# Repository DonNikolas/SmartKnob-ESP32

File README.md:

# SmartKnob-ESP32
Sound-controlled haptic smart knob for smart home control — ESP32-S3, FOC motor feedback, clap detection, MQTT/Home Assistant

## 3D-Render

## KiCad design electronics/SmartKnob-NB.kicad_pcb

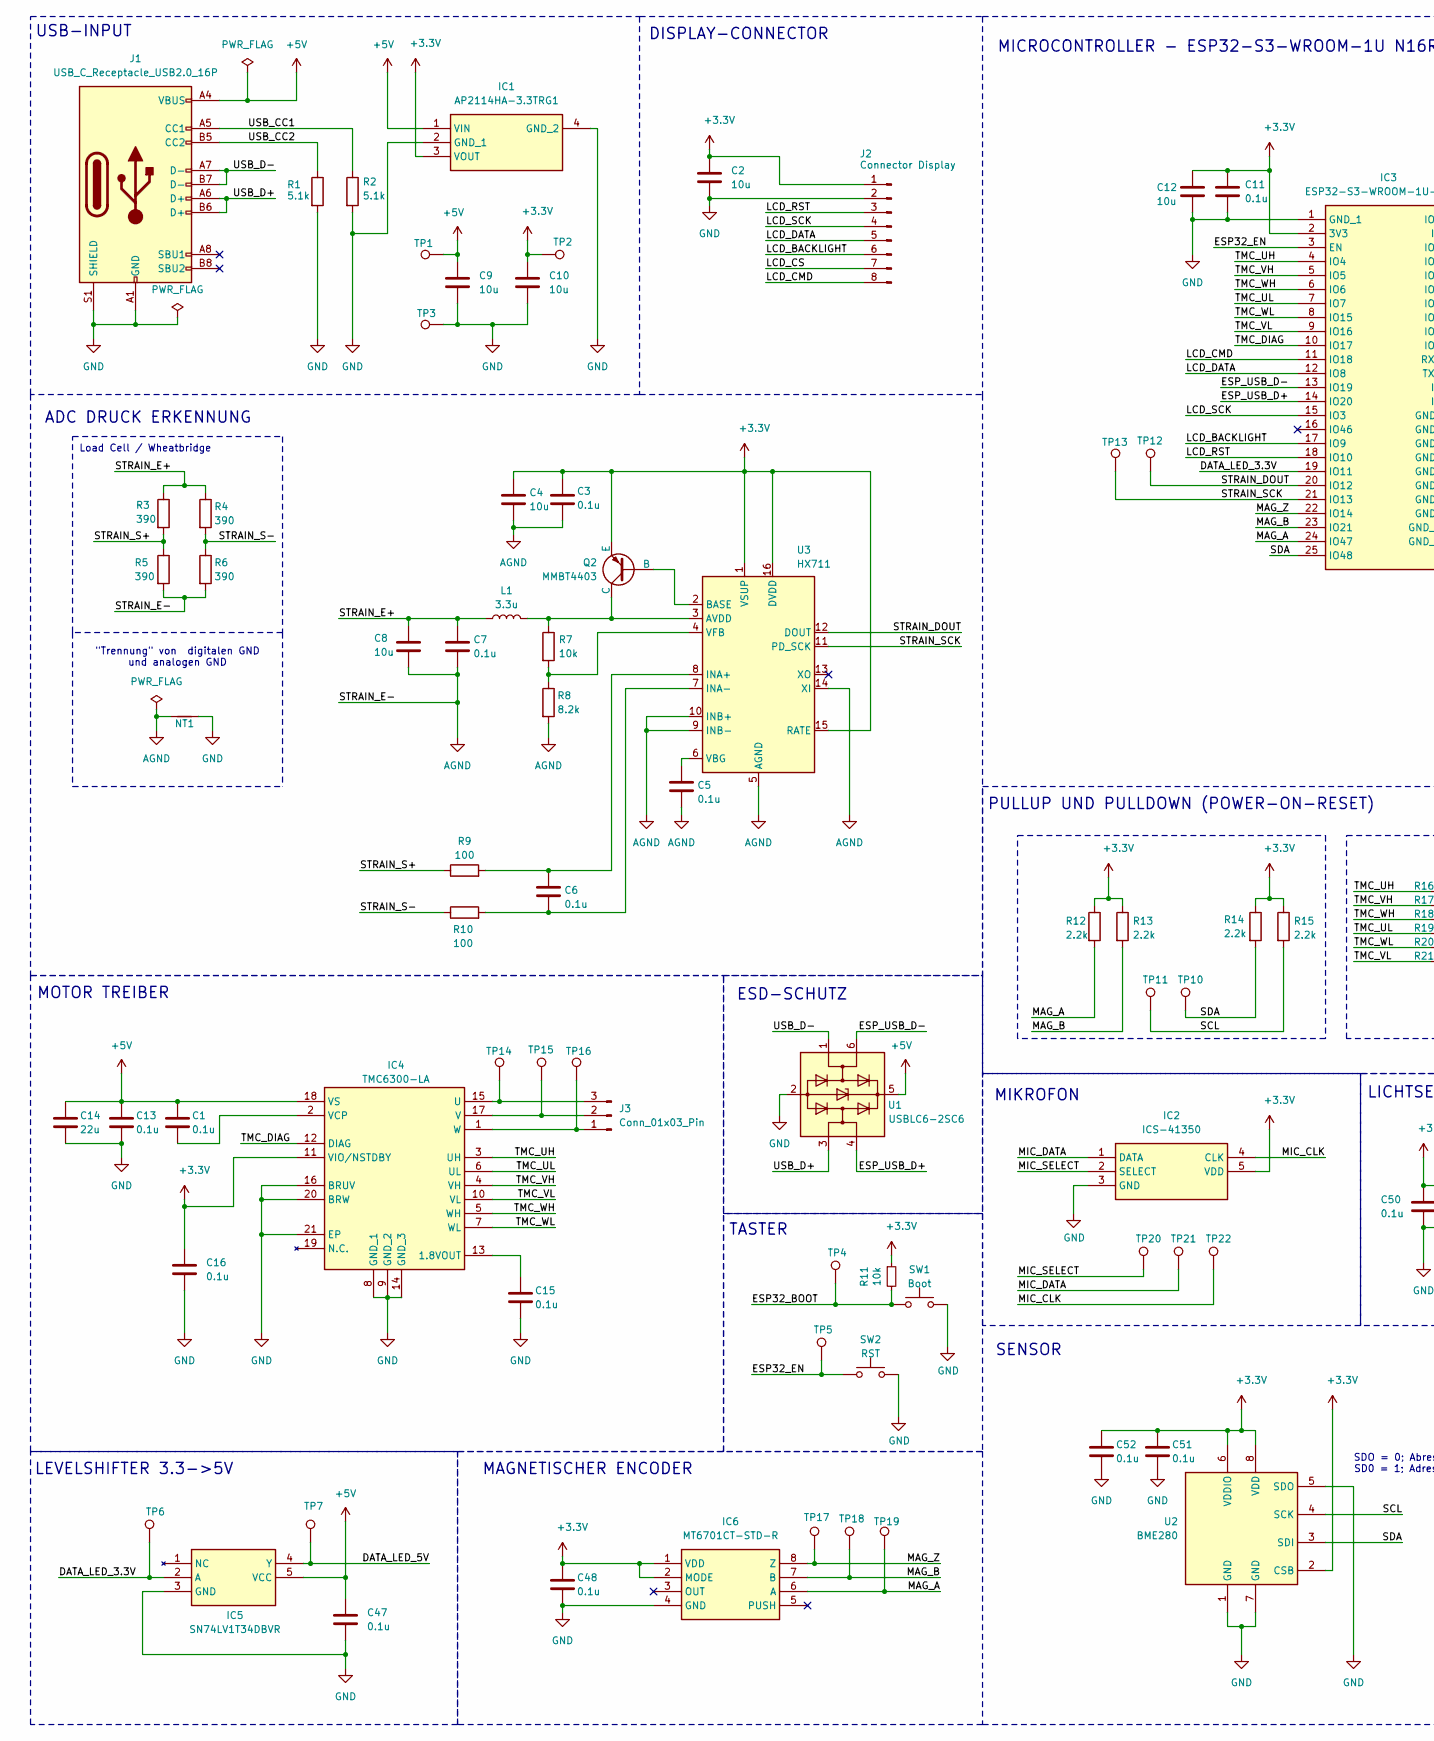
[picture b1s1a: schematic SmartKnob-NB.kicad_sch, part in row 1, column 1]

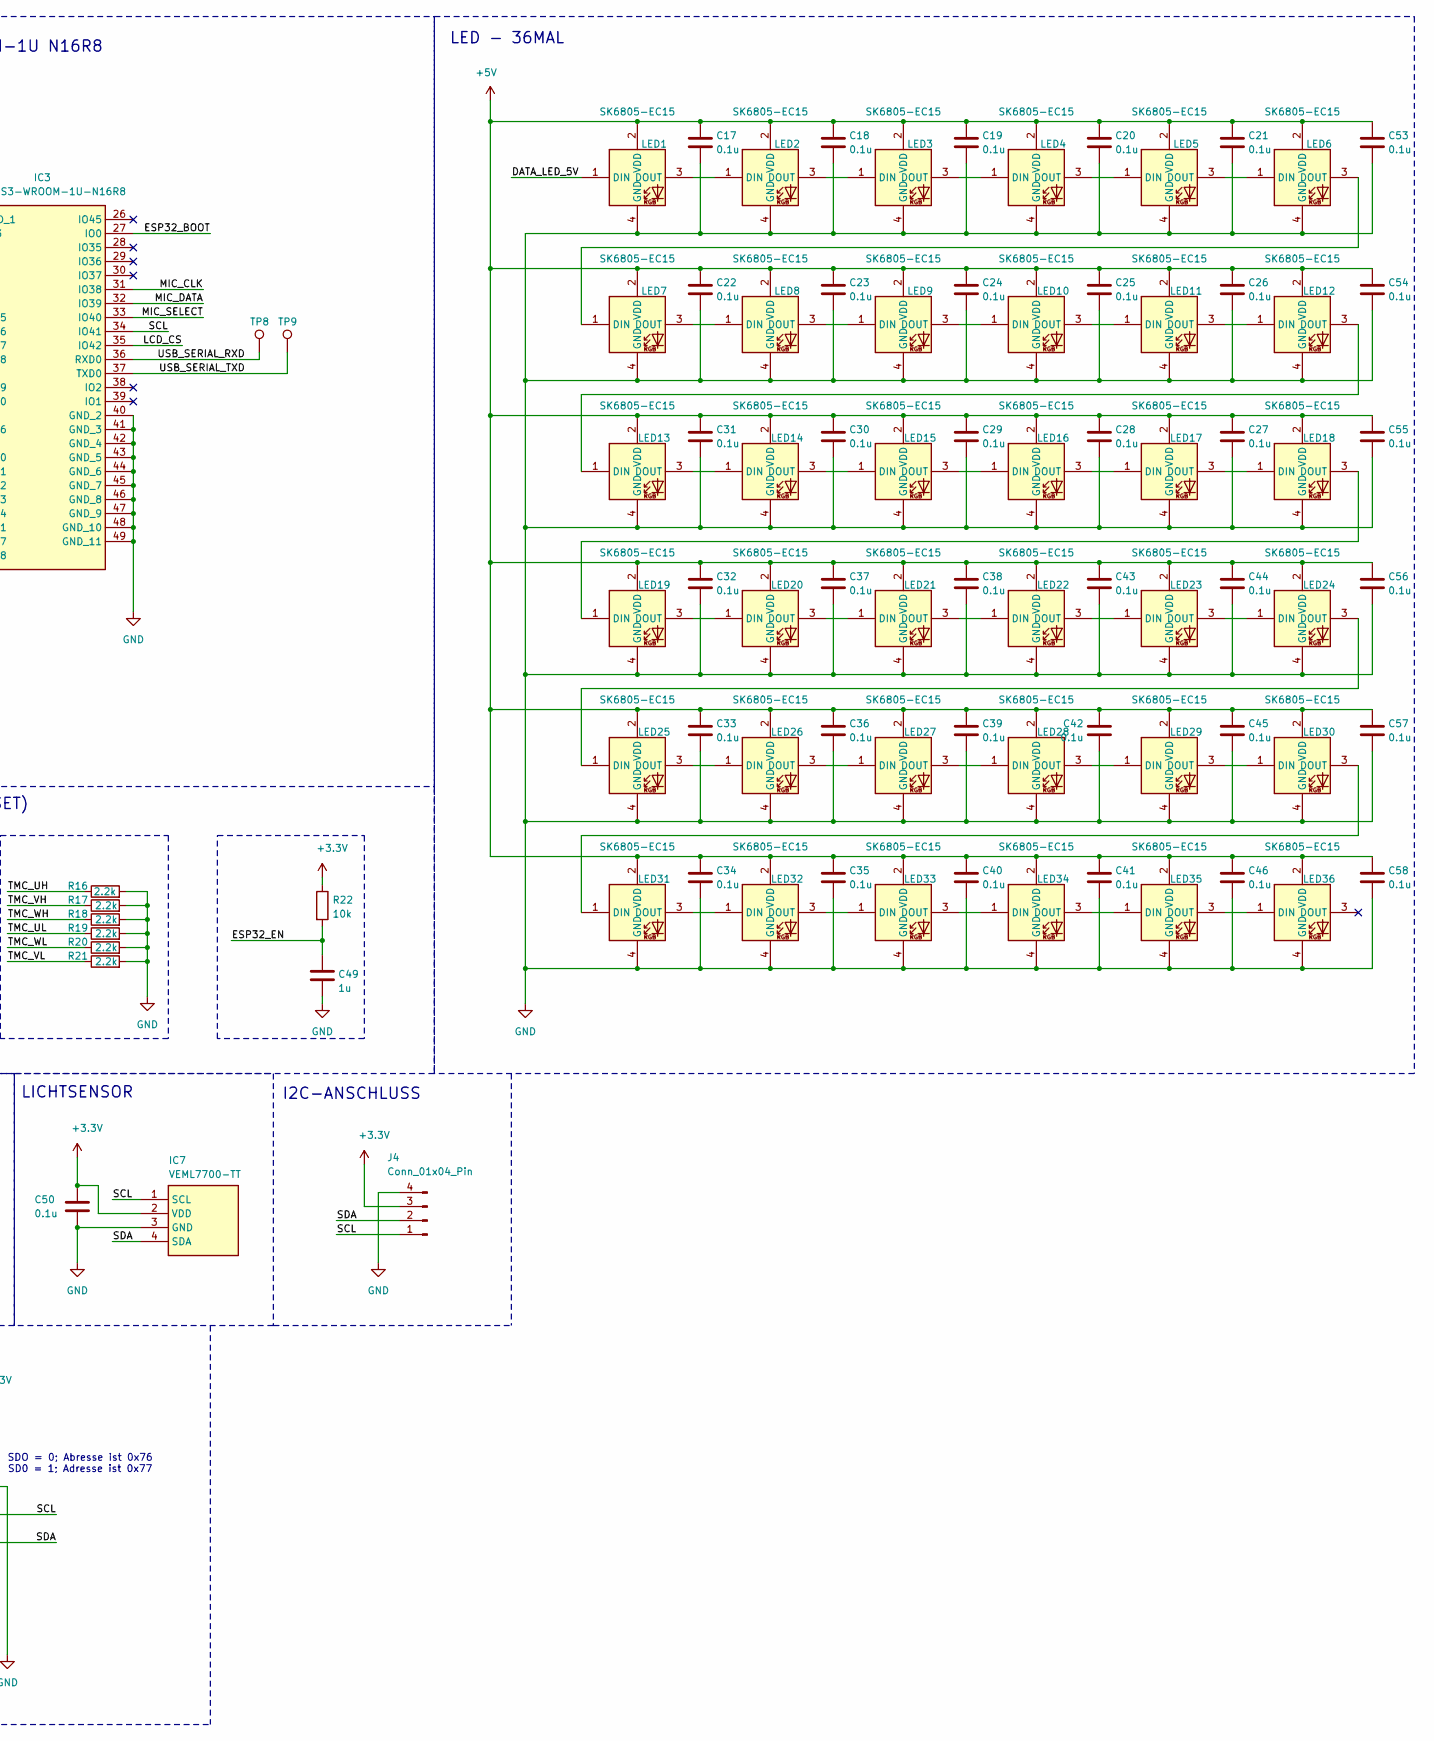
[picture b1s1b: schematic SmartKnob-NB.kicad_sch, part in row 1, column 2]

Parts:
C1, C3, C5, C6, C7, C11, C13, C15, C16, C17, C18, C19, C20, C21, C22, C23, C24, C25, C26, C27, C28, C29, C30, C31, C32, C33, C34, C35, C36, C37, C38, C39, C40, C41, C42, C43, C44, C45, C46, C47, C48, C50, C51, C52, C53, C54, C55, C56, C57, C58: 0.1u; C_0402_1005Metric_Pad0.74x0.62mm_HandSolder
C2, C9, C10, C12: 10u; C_0603_1608Metric_Pad1.08x0.95mm_HandSolder
C4, C8: 10u; C_0805_2012Metric_Pad1.18x1.45mm_HandSolder
C14: 22u; C_0603_1608Metric_Pad1.08x0.95mm_HandSolder
C49: 1u; C_0603_1608Metric_Pad1.08x0.95mm_HandSolder
IC1: AP2114HA-3.3TRG1; SOT230P700X180-4N; Manufacturer_Part_Number AP2114HA-3.3TRG1; Mouser Part Number 621-AP2114HA-3.3TRG1
IC2: ICS-41350; ICS41352; Manufacturer_Part_Number ICS-41350; Mouser Part Number 410-ICS-41350
IC3: ESP32-S3-WROOM-1U-N16R8; ESP32S3WROOM1UN16R8; Manufacturer_Part_Number ESP32-S3-WROOM-1U-N16R8; Mouser Part Number 356-ESP32S3WM1UN16R8
IC4: TMC6300-LA; QFN40P300X300X90-21N; Manufacturer_Part_Number TMC6300-LA; Mouser Part Number 700-TMC6300-LA
IC5: SN74LV1T34DBVR; SOT95P280X145-5N; Manufacturer_Part_Number SN74LV1T34DBVR; Mouser Part Number 595-SN74LV1T34DBVR
IC6: MT6701CT-STD-R; SOIC127P600X175-8N; Manufacturer_Part_Number MT6701CT-STD-R
IC7: VEML7700-TT; VEML7700; Manufacturer_Part_Number VEML7700-TT; Mouser Part Number 78-VEML7700-TT
J1: USB_C_Receptacle_USB2.0_16P; USB4510031A
J2: Connector Display; Unbenannt
J3: Conn_01x03_Pin; Molex_CLIK-Mate_502386-0370_1x03-1MP_P1.25mm_Horizontal
J4: Conn_01x04_Pin; Unbenannt
L1: 3.3u; L_0805_2012Metric_Pad1.05x1.20mm_HandSolder
LED1, LED2, LED3, LED4, LED5, LED6, LED7, LED8, LED9, LED10, LED11, LED12, LED13, LED14, LED15, LED16, LED17, LED18, LED19, LED20, LED21, LED22, LED23, LED24, LED25, LED26, LED27, LED28, LED29, LED30, LED31, LED32, LED33, LED34, LED35, LED36: SK6805-EC15; SK6805EC15; Manufacturer_Part_Number SK6805-EC15
NT1: NetTie_2; NetTie-2_SMD_Pad0.5mm
Q2: MMBT4403; SOT95P248X115-3N
R1, R2: 5.1k; R_0402_1005Metric_Pad0.72x0.64mm_HandSolder
R3, R4, R5, R6: 390; D_2512_6332Metric
R7, R22: 10k; R_0402_1005Metric_Pad0.72x0.64mm_HandSolder
R8: 8.2k; R_0402_1005Metric_Pad0.72x0.64mm_HandSolder
R9, R10: 100; R_0402_1005Metric_Pad0.72x0.64mm_HandSolder
R11: 10k; R_0402_1005Metric_Pad0.72x0.64mm_HandSolder; LCSC C98220
R12, R13, R14, R15, R16, R17, R18, R19, R20, R21: 2.2k; R_0402_1005Metric_Pad0.72x0.64mm_HandSolder
SW1: Boot; KSS241GLFS; LCSC C116501
SW2: RST; KSS241GLFS; LCSC C116501
TP1, TP2, TP3, TP4, TP5, TP6, TP7, TP8, TP9, TP10, TP11, TP12, TP13, TP14, TP15, TP16, TP17, TP18, TP19, TP20, TP21, TP22: TestPoint; TestPoint_Pad_1.5x1.5mm
U1: USBLC6-2SC6; SOT-23-6_Handsoldering; LCSC C7519
U2: BME280; Bosch_LGA-8_2.5x2.5mm_P0.65mm_ClockwisePinNumbering
U3: HX711; SOP-16_4.4x10.4mm_P1.27mm

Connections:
+3.3V: C2.1, C3.1, C4.1, C10.1, C11.1, C12.1, C16.1, C48.1, C50.1, C51.1, C52.1, IC1.3 (VOUT), IC2.5 (VDD), IC3.2 (3V3), IC4.11 (VIO/NSTDBY), IC6.1 (VDD), IC6.2 (MODE), IC7.2 (VDD), J2.1, J4.3, Q2.3 (E), R11.1, R12.1, R13.1, R14.1, R15.1, R22.1, TP2.1 (1_1), U2.2 (CSB), U2.6 (VDDIO), U2.8 (VDD), U3.1 (VSUP), U3.15 (RATE), U3.16 (DVDD)
+5V: C1.1, C9.1, C13.1, C14.1, C17.1, C18.1, C19.1, C20.1, C21.1, C22.1, C23.1, C24.1, C25.1, C26.1, C27.1, C28.1, C29.1, C30.1, C31.1, C32.1, C33.1, C34.1, C35.1, C36.1, C37.1, C38.1, C39.1, C40.1, C41.1, C42.1, C43.1, C44.1, C45.1, C46.1, C47.1, C53.1, C54.1, C55.1, C56.1, C57.1, C58.1, IC1.1 (VIN), IC4.18 (VS), IC5.5 (VCC), J1.A4 (VBUS), J1.A9 (VBUS), J1.B4 (VBUS), J1.B9 (VBUS), LED1.2 (VDD), LED2.2 (VDD), LED3.2 (VDD), LED4.2 (VDD), LED5.2 (VDD), LED6.2 (VDD), LED7.2 (VDD), LED8.2 (VDD), LED9.2 (VDD), LED10.2 (VDD), LED11.2 (VDD), LED12.2 (VDD), LED13.2 (VDD), LED14.2 (VDD), LED15.2 (VDD), LED16.2 (VDD), LED17.2 (VDD), LED18.2 (VDD), LED19.2 (VDD), LED20.2 (VDD), LED21.2 (VDD), LED22.2 (VDD), LED23.2 (VDD), LED24.2 (VDD), LED25.2 (VDD), LED26.2 (VDD), LED27.2 (VDD), LED28.2 (VDD), LED29.2 (VDD), LED30.2 (VDD), LED31.2 (VDD), LED32.2 (VDD), LED33.2 (VDD), LED34.2 (VDD), LED35.2 (VDD), LED36.2 (VDD), TP1.1 (1_1), U1.5 (VBUS)
/DATA_LED_3.3V: IC3.19 (IO11), IC5.2 (A), TP6.1 (1_1)
/DATA_LED_5V: IC5.4 (Y), LED1.1 (DIN), TP7.1 (1_1)
/ESP32_BOOT: IC3.27 (IO0), R11.2, SW1.1, TP4.1 (1_1)
/ESP32_EN: C49.1, IC3.3 (EN), R22.2, SW2.1, TP5.1 (1_1)
/ESP_USB_D+: IC3.14 (IO20), U1.4 (I/O2)
/ESP_USB_D-: IC3.13 (IO19), U1.6 (I/O1)
/LCD_BACKLIGHT: IC3.17 (IO9), J2.6
/LCD_CMD: IC3.11 (IO18), J2.8
/LCD_CS: IC3.35 (IO42), J2.7
/LCD_DATA: IC3.12 (IO8), J2.5
/LCD_RST: IC3.18 (IO10), J2.3
/LCD_SCK: IC3.15 (IO3), J2.4
/MAG_A: IC3.24 (IO47), IC6.6 (A), R12.2, TP19.1 (1_1)
/MAG_B: IC3.23 (IO21), IC6.7 (B), R13.2, TP18.1 (1_1)
/MAG_Z: IC3.22 (IO14), IC6.8 (Z), TP17.1 (1_1)
/MIC_CLK: IC2.4 (CLK), IC3.31 (IO38), TP22.1 (1_1)
/MIC_DATA: IC2.1 (DATA), IC3.32 (IO39), TP21.1 (1_1)
/MIC_SELECT: IC2.2 (SELECT), IC3.33 (IO40), TP20.1 (1_1)
/SCL: IC3.34 (IO41), IC7.1 (SCL), J4.1, R15.2, TP11.1 (1_1), U2.4 (SCK)
/SDA: IC3.25 (IO48), IC7.4 (SDA), J4.2, R14.2, TP10.1 (1_1), U2.3 (SDI)
/STRAIN_DOUT: IC3.20 (IO12), TP12.1 (1_1), U3.12 (DOUT)
/STRAIN_E+: C7.1, C8.1, L1.1, R3.1, R4.1
/STRAIN_S+: R3.2, R5.1, R9.1
/STRAIN_S-: R4.2, R6.1, R10.1
/STRAIN_SCK: IC3.21 (IO13), TP13.1 (1_1), U3.11 (PD_SCK)
/TMC_DIAG: IC3.10 (IO17), IC4.12 (DIAG)
/TMC_UH: IC3.4 (IO4), IC4.3 (UH), R16.1
/TMC_UL: IC3.7 (IO7), IC4.6 (UL), R19.1
/TMC_VH: IC3.5 (IO5), IC4.4 (VH), R17.1
/TMC_VL: IC3.9 (IO16), IC4.10 (VL), R21.1
/TMC_WH: IC3.6 (IO6), IC4.5 (WH), R18.1
/TMC_WL: IC3.8 (IO15), IC4.7 (WL), R20.1
/USB_CC1: J1.A5 (CC1), R2.1
/USB_CC2: J1.B5 (CC2), R1.1
/USB_D+: J1.A6 (D+), J1.B6 (D+), U1.3 (I/O2)
/USB_D-: J1.A7 (D-), J1.B7 (D-), U1.1 (I/O1)
/USB_SERIAL_RXD: IC3.36 (RXD0), TP8.1 (1_1)
/USB_SERIAL_TXD: IC3.37 (TXD0), TP9.1 (1_1)
AGND: C3.2, C4.2, C5.2, C7.2, C8.2, NT1.1, R5.2, R6.2, R8.2, U3.5 (AGND), U3.9 (INB-), U3.10 (INB+), U3.14 (XI)
GND: C2.2, C9.2, C10.2, C11.2, C12.2, C13.2, C14.2, C15.2, C16.2, C17.2, C18.2, C19.2, C20.2, C21.2, C22.2, C23.2, C24.2, C25.2, C26.2, C27.2, C28.2, C29.2, C30.2, C31.2, C32.2, C33.2, C34.2, C35.2, C36.2, C37.2, C38.2, C39.2, C40.2, C41.2, C42.2, C43.2, C44.2, C45.2, C46.2, C47.2, C48.2, C49.2, C50.2, C51.2, C52.2, C53.2, C54.2, C55.2, C56.2, C57.2, C58.2, IC1.2 (GND_1), IC1.4 (GND_2), IC2.3 (GND), IC3.1 (GND_1), IC3.40 (GND_2), IC3.41 (GND_3), IC3.42 (GND_4), IC3.43 (GND_5), IC3.44 (GND_6), IC3.45 (GND_7), IC3.46 (GND_8), IC3.47 (GND_9), IC3.48 (GND_10), IC3.49 (GND_11), IC4.8 (GND_1), IC4.9 (GND_2), IC4.14 (GND_3), IC4.16 (BRUV), IC4.20 (BRW), IC4.21 (EP), IC5.3 (GND), IC6.4 (GND), IC7.3 (GND), J1.A1 (GND), J1.A12 (GND), J1.B1 (GND), J1.B12 (GND), J1.S1 (SHIELD), J2.2, J4.4, LED1.4 (GND), LED2.4 (GND), LED3.4 (GND), LED4.4 (GND), LED5.4 (GND), LED6.4 (GND), LED7.4 (GND), LED8.4 (GND), LED9.4 (GND), LED10.4 (GND), LED11.4 (GND), LED12.4 (GND), LED13.4 (GND), LED14.4 (GND), LED15.4 (GND), LED16.4 (GND), LED17.4 (GND), LED18.4 (GND), LED19.4 (GND), LED20.4 (GND), LED21.4 (GND), LED22.4 (GND), LED23.4 (GND), LED24.4 (GND), LED25.4 (GND), LED26.4 (GND), LED27.4 (GND), LED28.4 (GND), LED29.4 (GND), LED30.4 (GND), LED31.4 (GND), LED32.4 (GND), LED33.4 (GND), LED34.4 (GND), LED35.4 (GND), LED36.4 (GND), NT1.2, R1.2, R2.2, R16.2, R17.2, R18.2, R19.2, R20.2, R21.2, SW1.2, SW2.2, TP3.1 (1_1), U1.2 (GND), U2.1 (GND), U2.5 (SDO), U2.7 (GND)
unnamed: C15.1, IC4.13 (1.8VOUT)
unnamed: IC4.15 (U), J3.3, TP14.1 (1_1)
unnamed: IC4.17 (V), J3.2, TP15.1 (1_1)
unnamed: C1.2, IC4.2 (VCP)
unnamed: IC4.1 (W), J3.1, TP16.1 (1_1)
unnamed: LED1.3 (DOUT), LED2.1 (DIN)
unnamed: LED2.3 (DOUT), LED3.1 (DIN)
unnamed: LED3.3 (DOUT), LED4.1 (DIN)
unnamed: LED4.3 (DOUT), LED5.1 (DIN)
unnamed: LED5.3 (DOUT), LED6.1 (DIN)
unnamed: LED6.3 (DOUT), LED7.1 (DIN)
unnamed: LED7.3 (DOUT), LED8.1 (DIN)
unnamed: LED8.3 (DOUT), LED9.1 (DIN)
unnamed: LED9.3 (DOUT), LED10.1 (DIN)
unnamed: LED10.3 (DOUT), LED11.1 (DIN)
unnamed: LED11.3 (DOUT), LED12.1 (DIN)
unnamed: LED12.3 (DOUT), LED13.1 (DIN)
unnamed: LED13.3 (DOUT), LED14.1 (DIN)
unnamed: LED14.3 (DOUT), LED15.1 (DIN)
unnamed: LED15.3 (DOUT), LED16.1 (DIN)
unnamed: LED16.3 (DOUT), LED17.1 (DIN)
unnamed: LED17.3 (DOUT), LED18.1 (DIN)
unnamed: LED18.3 (DOUT), LED19.1 (DIN)
unnamed: LED19.3 (DOUT), LED20.1 (DIN)
unnamed: LED20.3 (DOUT), LED21.1 (DIN)
unnamed: LED21.3 (DOUT), LED22.1 (DIN)
unnamed: LED22.3 (DOUT), LED23.1 (DIN)
unnamed: LED23.3 (DOUT), LED24.1 (DIN)
unnamed: LED24.3 (DOUT), LED25.1 (DIN)
unnamed: LED25.3 (DOUT), LED26.1 (DIN)
unnamed: LED26.3 (DOUT), LED27.1 (DIN)
unnamed: LED27.3 (DOUT), LED28.1 (DIN)
unnamed: LED28.3 (DOUT), LED29.1 (DIN)
unnamed: LED29.3 (DOUT), LED30.1 (DIN)
unnamed: LED30.3 (DOUT), LED31.1 (DIN)
unnamed: LED31.3 (DOUT), LED32.1 (DIN)
unnamed: LED32.3 (DOUT), LED33.1 (DIN)
unnamed: LED33.3 (DOUT), LED34.1 (DIN)
unnamed: LED34.3 (DOUT), LED35.1 (DIN)
unnamed: LED35.3 (DOUT), LED36.1 (DIN)
unnamed: Q2.2 (B), U3.2 (BASE)
unnamed: L1.2, Q2.1 (C), R7.1, U3.3 (AVDD)
unnamed: C6.1, R9.2, U3.8 (INA+)
unnamed: C6.2, R10.2, U3.7 (INA-)
unnamed: C5.1, U3.6 (VBG)
unnamed: R7.2, R8.1, U3.4 (VFB)

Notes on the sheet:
LEVELSHIFTER 3.3->5V
TASTER
ADC DRUCK ERKENNUNG
Load Cell / Wheatbridge
I2C-ANSCHLUSS
LED - 36MAL
"Trennung" von digitalen GND und analogen GND
MAGNETISCHER ENCODER
USB-INPUT
SENSOR
MICROCONTROLLER - ESP32-S3-WROOM-1U N16R8
MOTOR TREIBER
MIKROFON
LICHTSENSOR
SDO = 0; Abresse ist 0x76 SD0 = 1; Adresse ist 0x77
PULLUP UND PULLDOWN (POWER-ON-RESET)
ESD-SCHUTZ
DISPLAY-CONNECTOR

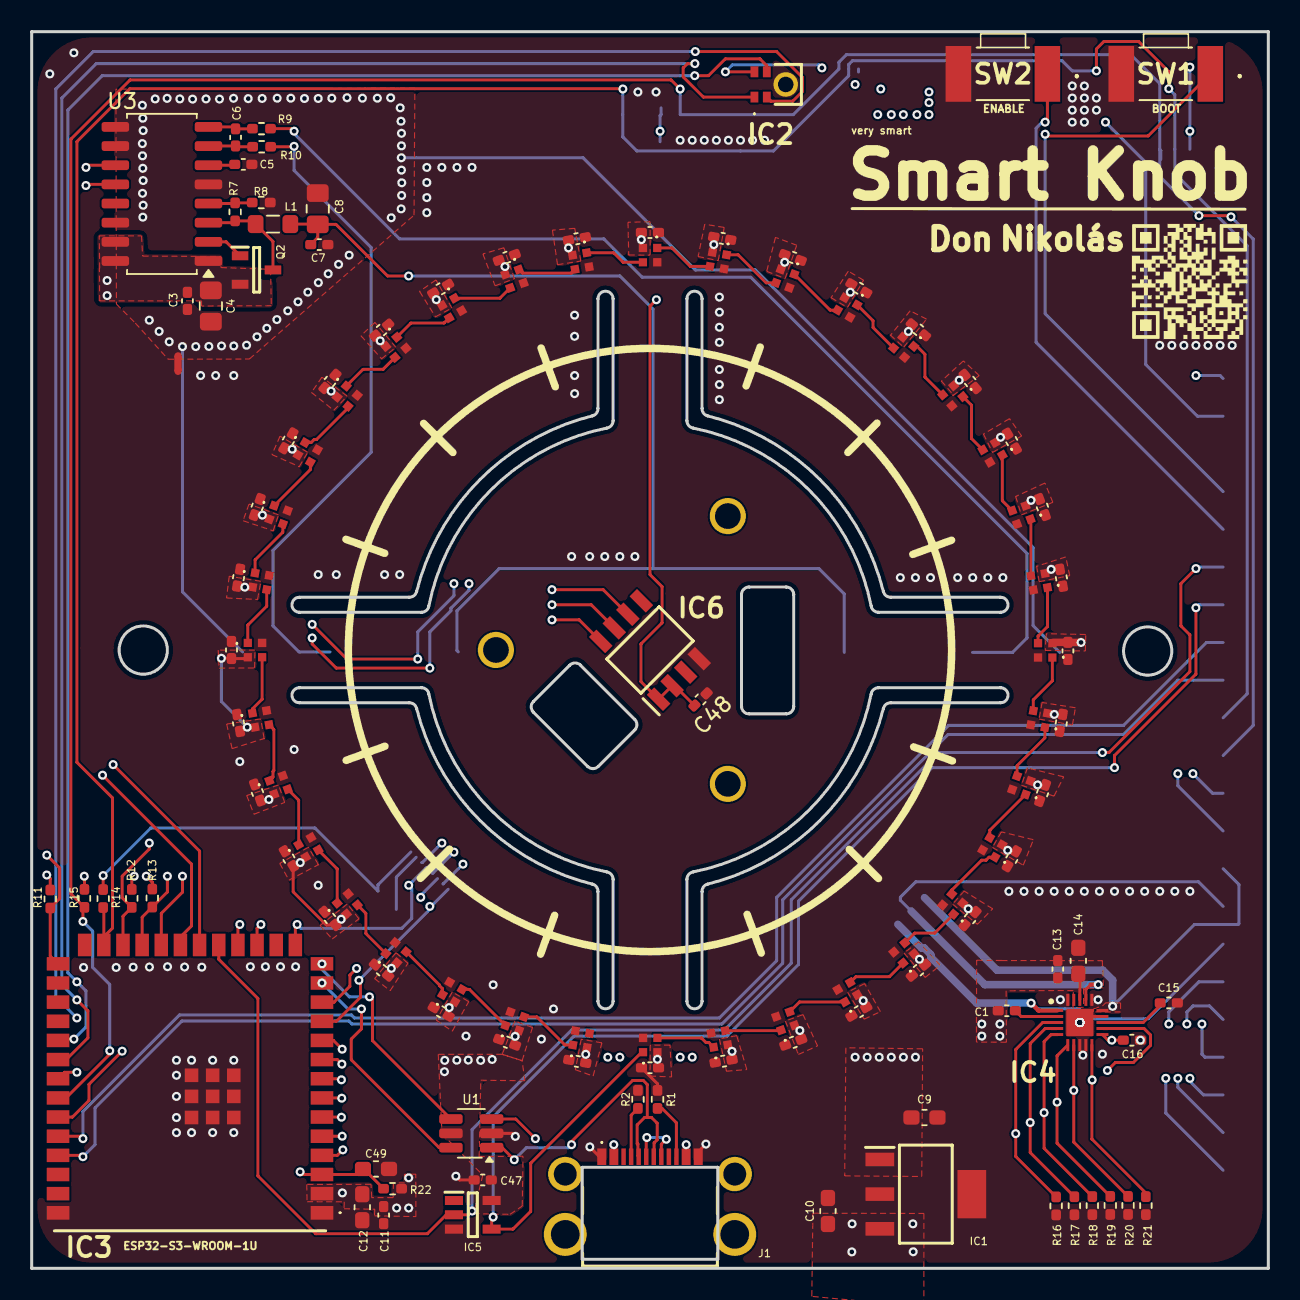
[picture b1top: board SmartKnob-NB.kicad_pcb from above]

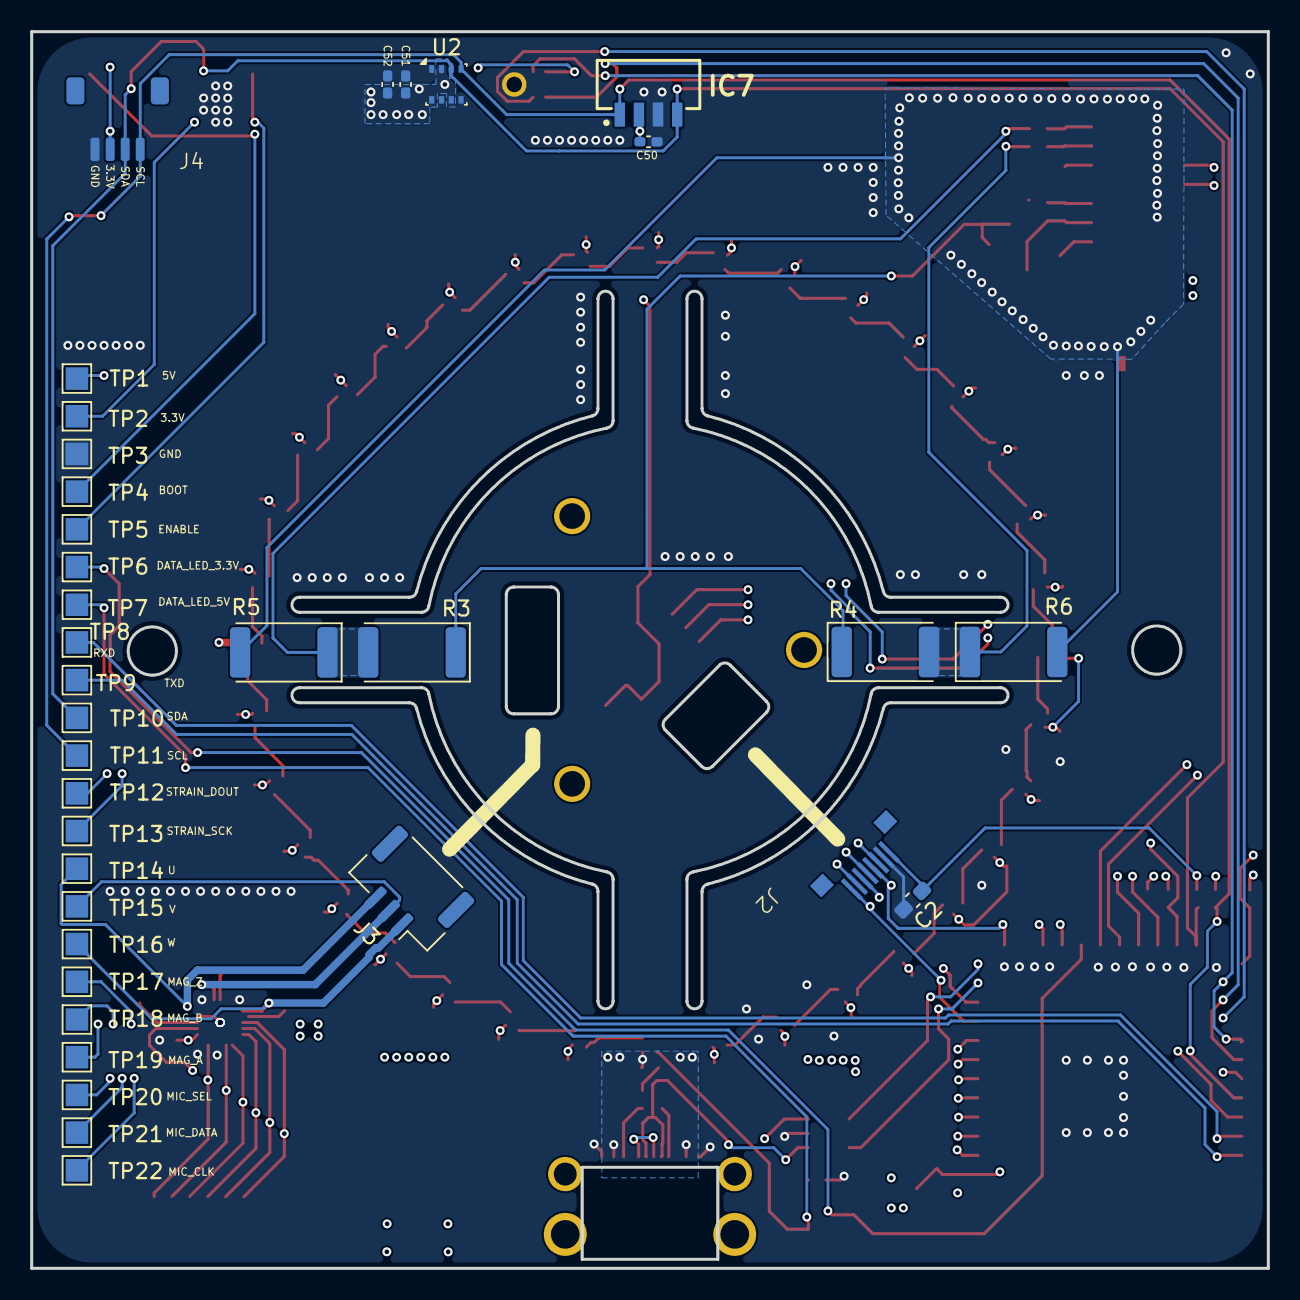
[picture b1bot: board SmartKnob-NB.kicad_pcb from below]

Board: 4 copper layers, 82.0 x 82.0 mm, 157 parts (35 on the bottom side), 88 nets.

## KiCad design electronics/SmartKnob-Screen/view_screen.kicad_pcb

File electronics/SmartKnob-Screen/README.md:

# SmartKnob Screen PCB

The screen PCB design was copied unchanged from SeedLabs.

Source: https://github.com/SeedLabs-it/smartknob-hardware

The original files are stored here for use with my SmartKnob project.
This PCB was not designed by me.

See license.md for the original SeedLabs hardware license.

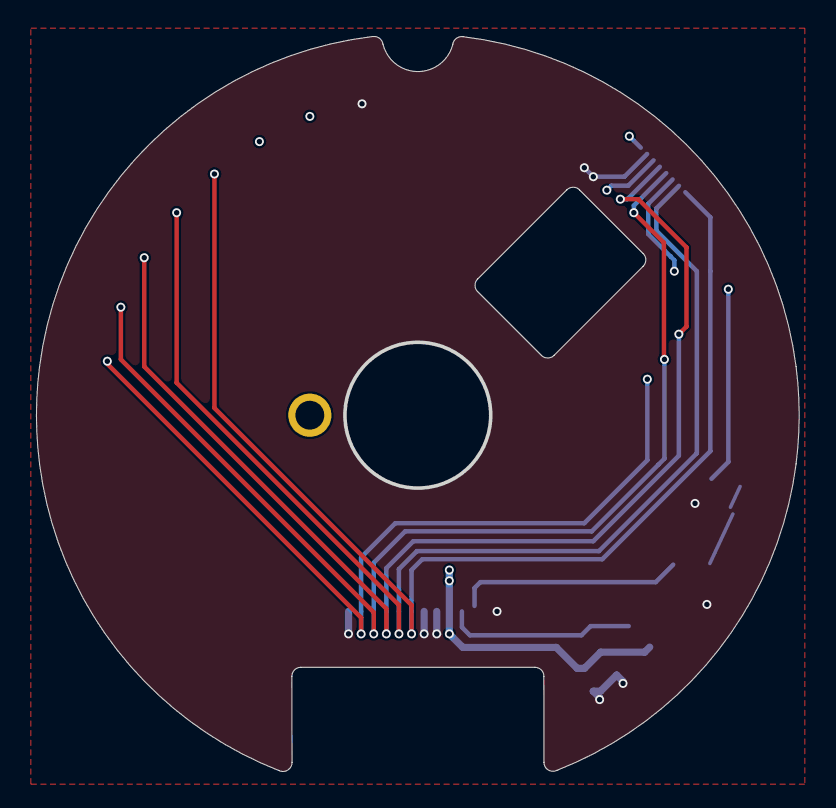
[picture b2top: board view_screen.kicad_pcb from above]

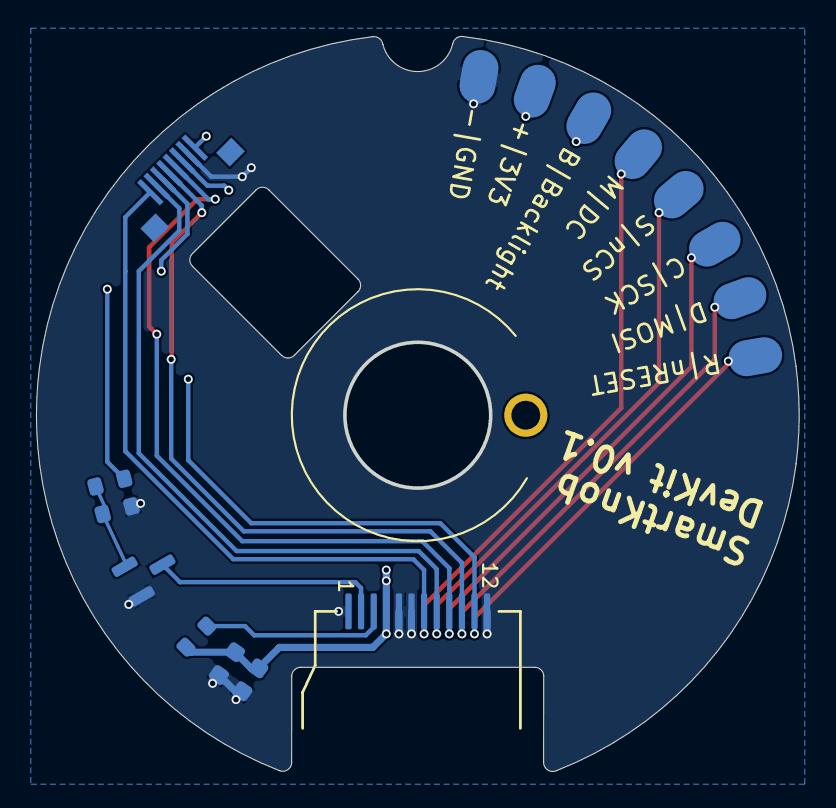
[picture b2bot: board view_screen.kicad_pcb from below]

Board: 4 copper layers, 42.4 x 40.8 mm, 17 parts (16 on the bottom side), 11 nets.

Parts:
C1: 22uF; C_0603_1608Metric
C2: 0.1uF; C_0603_1608Metric
H1: AlignmentHole; AlignmentHole_1.6
J2: GC9A01; GC9A01Round1.28
J6: LCD - FPC; Amphenol FCI FPC 8 pin 0.5 pitch
Q1: 2N7002; SOT-23
R1: 10k; R_0603_1608Metric
R2: 22R; R_0603_1608Metric
R3: 1M; R_0603_1608Metric
TP1: S|nCS; test_point_connectivity
TP2: C|SCK; test_point_connectivity
TP3: D|MOSI; test_point_connectivity
TP4: R|nRESET; test_point_connectivity
TP5: -|GND; test_point_connectivity
TP6: +|3V3; test_point_connectivity
TP7: B|Backlight; test_point_connectivity
TP8: M|DC; test_point_connectivity

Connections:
/BACKLIGHT_EN: J6.3, R1.1, TP7.1
/DC: J2.7, J6.1, TP8.1
/LEDA: J2.3, R2.2
/LEDK: J2.2, Q1.3 (D)
/MOSI: J2.10, J6.4, TP3.1
/SCK: J2.9, J6.5, TP2.1
/VDD: C1.1, C2.1, J2.4, J6.8, R2.1, TP6.1
/nCS: J2.8, J6.2, TP1.1
/nRESET: J2.11, J6.6, TP4.1
GND: C1.2, C2.2, J2.1, J2.5, J2.6, J2.12, J6.7, Q1.2 (S), R3.2, TP5.1
unnamed: Q1.1 (G), R1.2, R3.1

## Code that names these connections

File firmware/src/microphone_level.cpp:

// Generated with ChatGPT assistance based on my project requirements.
// Diagnostic level meter. Acoustic response is not yet verified.

#include <Arduino.h>
#include <Adafruit_NeoPixel.h>
#include <driver/i2s.h>
#include <esp_err.h>
#include <math.h>

constexpr uint8_t MIC_CLK = 38;
constexpr uint8_t MIC_DATA = 39;
constexpr uint8_t MIC_SELECT = 40;
constexpr uint8_t MOTOR_PINS[] = {4, 7, 5, 16, 6, 15};
constexpr uint8_t BACKLIGHT_PIN = 9;

constexpr uint8_t LED_PIN = 11;
constexpr uint16_t LED_COUNT = 36;
constexpr uint32_t SAMPLE_RATE = 16000;
constexpr size_t FRAMES = 256;
constexpr i2s_port_t MIC_PORT = I2S_NUM_0;

Adafruit_NeoPixel ring(LED_COUNT, LED_PIN, NEO_GRB + NEO_KHZ800);

int16_t input[FRAMES * 2];
size_t filledBytes = 0;

// Digital RMS level that fills the complete ring.
// This affects the display scale, not microphone gain.
float fullScale = 3200.0f;
float shownLevel = 0.0f;
float reportPeak[2] = {};
uint32_t peakTime = 0;

void checkResult(esp_err_t result, const char* step) {
    if (result == ESP_OK) return;

    ring.clear();
    ring.show();
    Serial.printf("FAIL: %s: %s\n", step, esp_err_to_name(result));
    while (true) delay(1000);
}

float slotRms(unsigned slot) {
    double sum = 0;
    double squares = 0;

    for (size_t i = 0; i < FRAMES; i++) {
        const double value = input[2 * i + slot];
        sum += value;
        squares += value * value;
    }

    const double mean = sum / FRAMES;
    const double variance = squares / FRAMES - mean * mean;
    return static_cast<float>(sqrt(variance > 0 ? variance : 0));
}

void drawLevel(float level) {
    float fraction = level / fullScale;
    if (fraction > 1.0f) fraction = 1.0f;
    if (fraction < 0.0f) fraction = 0.0f;

    const uint16_t lit = static_cast<uint16_t>(
        fraction * LED_COUNT + 0.5f
    );

    ring.clear();
    for (uint16_t i = 0; i < lit; i++) {
        uint32_t colour;
        if (i < 24) {
            colour = ring.Color(0, 255, 0);
        } else if (i < 32) {
            colour = ring.Color(255, 140, 0);
        } else {
            colour = ring.Color(255, 0, 0);
        }
        ring.setPixelColor(i, colour);
    }
    ring.show();
}

void setup() {
    for (uint8_t pin : MOTOR_PINS) {
        pinMode(pin, OUTPUT);
        digitalWrite(pin, LOW);
    }
    pinMode(BACKLIGHT_PIN, OUTPUT);
    digitalWrite(BACKLIGHT_PIN, LOW);

    pinMode(MIC_SELECT, OUTPUT);
    digitalWrite(MIC_SELECT, LOW);

    Serial.begin(115200);
    delay(3000);

    ring.begin();
    ring.setBrightness(12);
    ring.clear();
    ring.show();

    Serial.println("\n=== SmartKnob microphone LED level test v1 ===");
    Serial.println("36 LEDs on GPIO 11. PDM clock target: 2.048 MHz.");
    Serial.println("Relative digital level, not calibrated dB SPL.");
    Serial.println("+ = more sensitive, - = less sensitive.");
    Serial.println("Red means display full scale, not ADC clipping.");

    i2s_config_t config = {};
    config.mode = static_cast<i2s_mode_t>(
        I2S_MODE_MASTER | I2S_MODE_RX | I2S_MODE_PDM
    );
    config.sample_rate = SAMPLE_RATE;
    config.bits_per_sample = I2S_BITS_PER_SAMPLE_16BIT;
    config.channel_format = I2S_CHANNEL_FMT_RIGHT_LEFT;
    config.communication_format = I2S_COMM_FORMAT_STAND_I2S;
    config.dma_buf_count = 8;
    config.dma_buf_len = FRAMES;
    config.use_apll = false;

    checkResult(
        i2s_driver_install(MIC_PORT, &config, 0, nullptr),
        "Install PDM driver"
    );

    i2s_pin_config_t pins = {};
    pins.mck_io_num = I2S_PIN_NO_CHANGE;
    pins.bck_io_num = I2S_PIN_NO_CHANGE;
    pins.ws_io_num = MIC_CLK;
    pins.data_out_num = I2S_PIN_NO_CHANGE;
    pins.data_in_num = MIC_DATA;

    checkResult(i2s_set_pin(MIC_PORT, &pins), "Configure pins");
    checkResult(
        i2s_set_pdm_rx_down_sample(MIC_PORT, I2S_PDM_DSR_16S),
        "Configure PDM conversion"
    );
}

void loop() {
    while (Serial.available()) {
        const char command = Serial.read();
        if (command == '+') {
            fullScale = fmaxf(1.0f, fullScale / 2.0f);
        } else if (command == '-') {
            fullScale = fminf(32768.0f, fullScale * 2.0f);
        } else {
            continue;
        }
        Serial.printf("Full-ring RMS level: %.1f\n", fullScale);
    }

    size_t bytesRead = 0;
    uint8_t* bytes = reinterpret_cast<uint8_t*>(input);
    const esp_err_t result = i2s_read(
        MIC_PORT, bytes + filledBytes, sizeof(input) - filledBytes,
        &bytesRead, pdMS_TO_TICKS(1000)
    );

    if (result != ESP_OK || bytesRead == 0) {
        ring.clear();
        ring.show();
        Serial.printf("READ ERROR: %s\n", esp_err_to_name(result));
        filledBytes = 0;
        shownLevel = 0;
        reportPeak[0] = reportPeak[1] = 0;
        delay(100);
        return;
    }

    filledBytes += bytesRead;
    if (filledBytes < sizeof(input)) return;
    filledBytes = 0;

    static uint32_t warmupStarted = millis();
    if (millis() - warmupStarted < 300) return;

    const float a = slotRms(0);
    const float b = slotRms(1);
    const float level = fmaxf(a, b);
    const uint32_t now = millis();

    reportPeak[0] = fmaxf(reportPeak[0], a);
    reportPeak[1] = fmaxf(reportPeak[1], b);

    // Fast rise, short peak hold and gradual fall.
    if (level >= shownLevel) {
        shownLevel = level;
        peakTime = now;
    } else if (now - peakTime > 150) {
        shownLevel = fmaxf(level, shownLevel * 0.92f);
    }

    static uint32_t lastDraw = 0;
    if (now - lastDraw >= 30) {
        drawLevel(shownLevel);
        lastDraw = now;
    }

    static uint32_t lastReport = 0;
    if (now - lastReport >= 250) {
        Serial.printf(
            "Time: %lu s | A RMSmax: %.1f | B RMSmax: %.1f"
            " | Full ring: %.1f\n",
            static_cast<unsigned long>(now / 1000),
            reportPeak[0], reportPeak[1], fullScale
        );
        reportPeak[0] = reportPeak[1] = 0;
        lastReport = now;
    }
}
